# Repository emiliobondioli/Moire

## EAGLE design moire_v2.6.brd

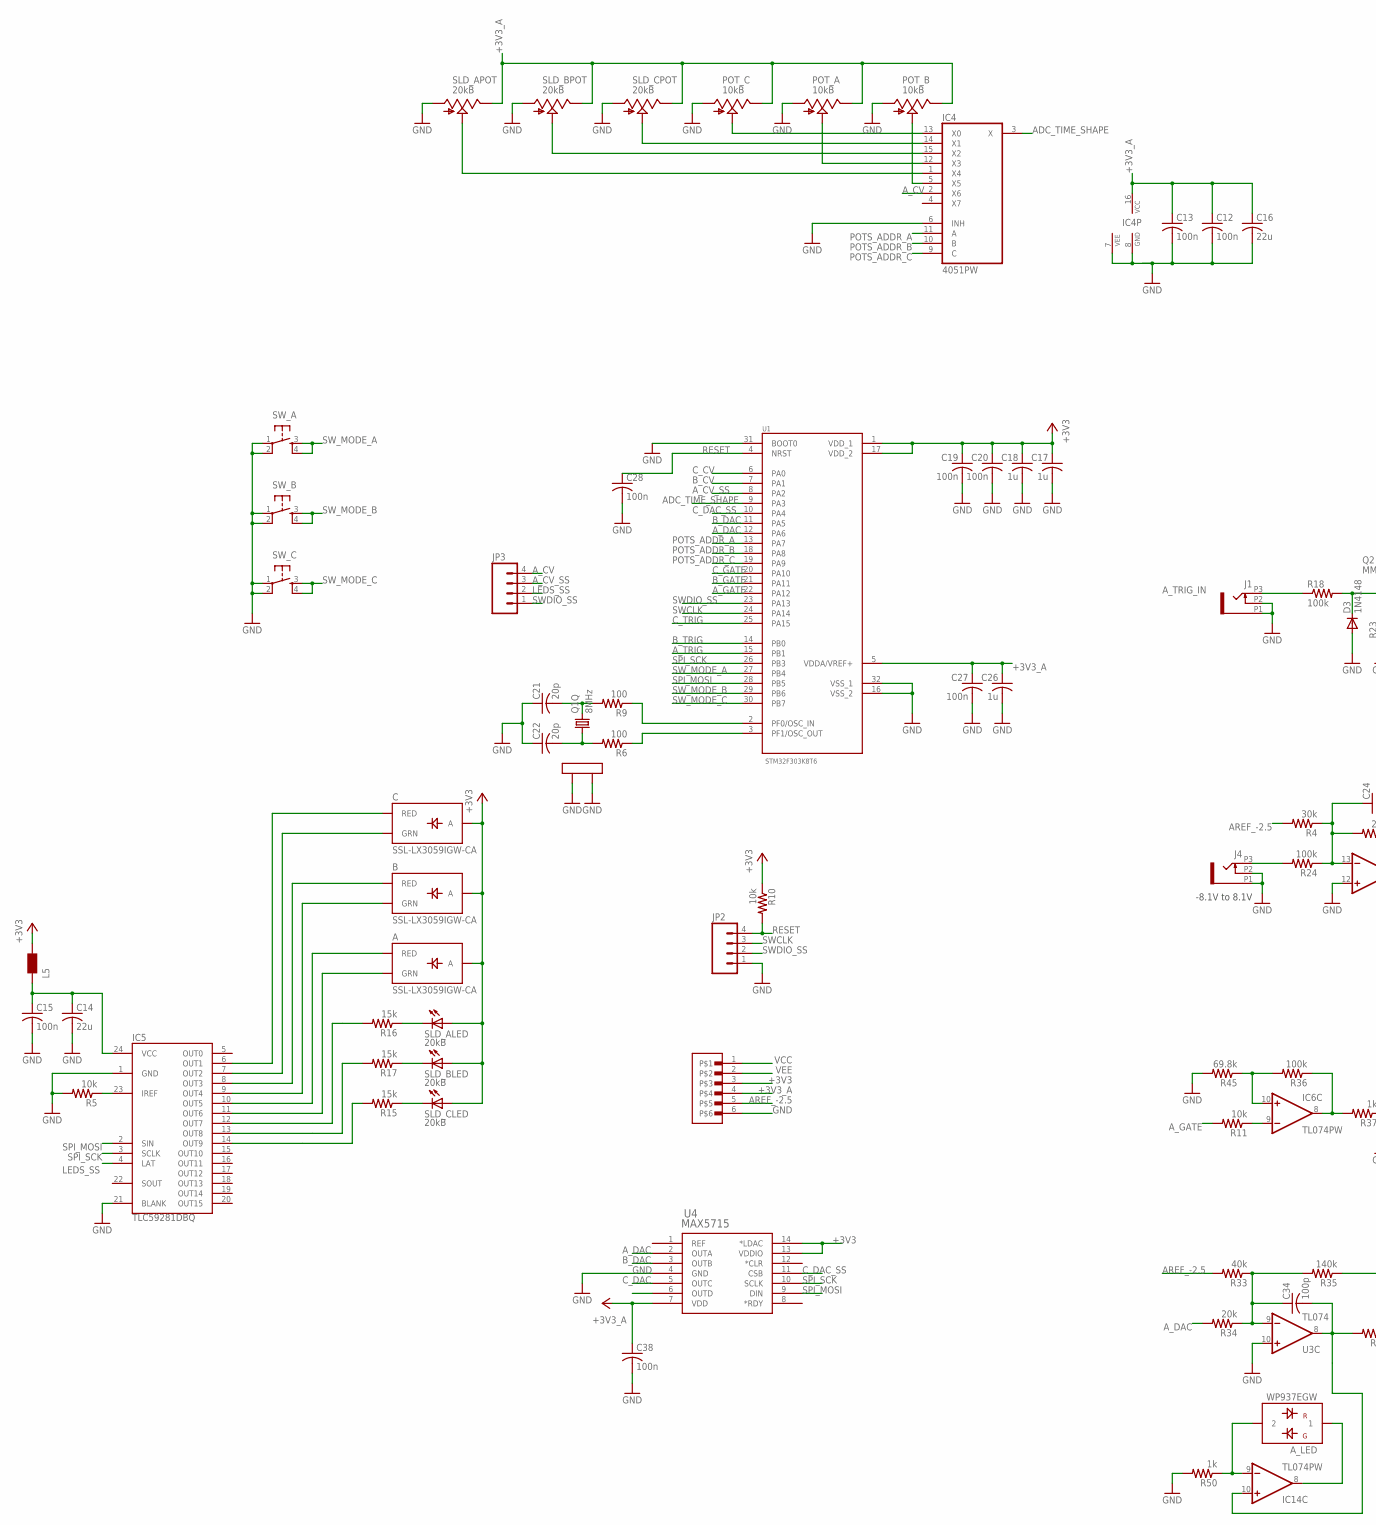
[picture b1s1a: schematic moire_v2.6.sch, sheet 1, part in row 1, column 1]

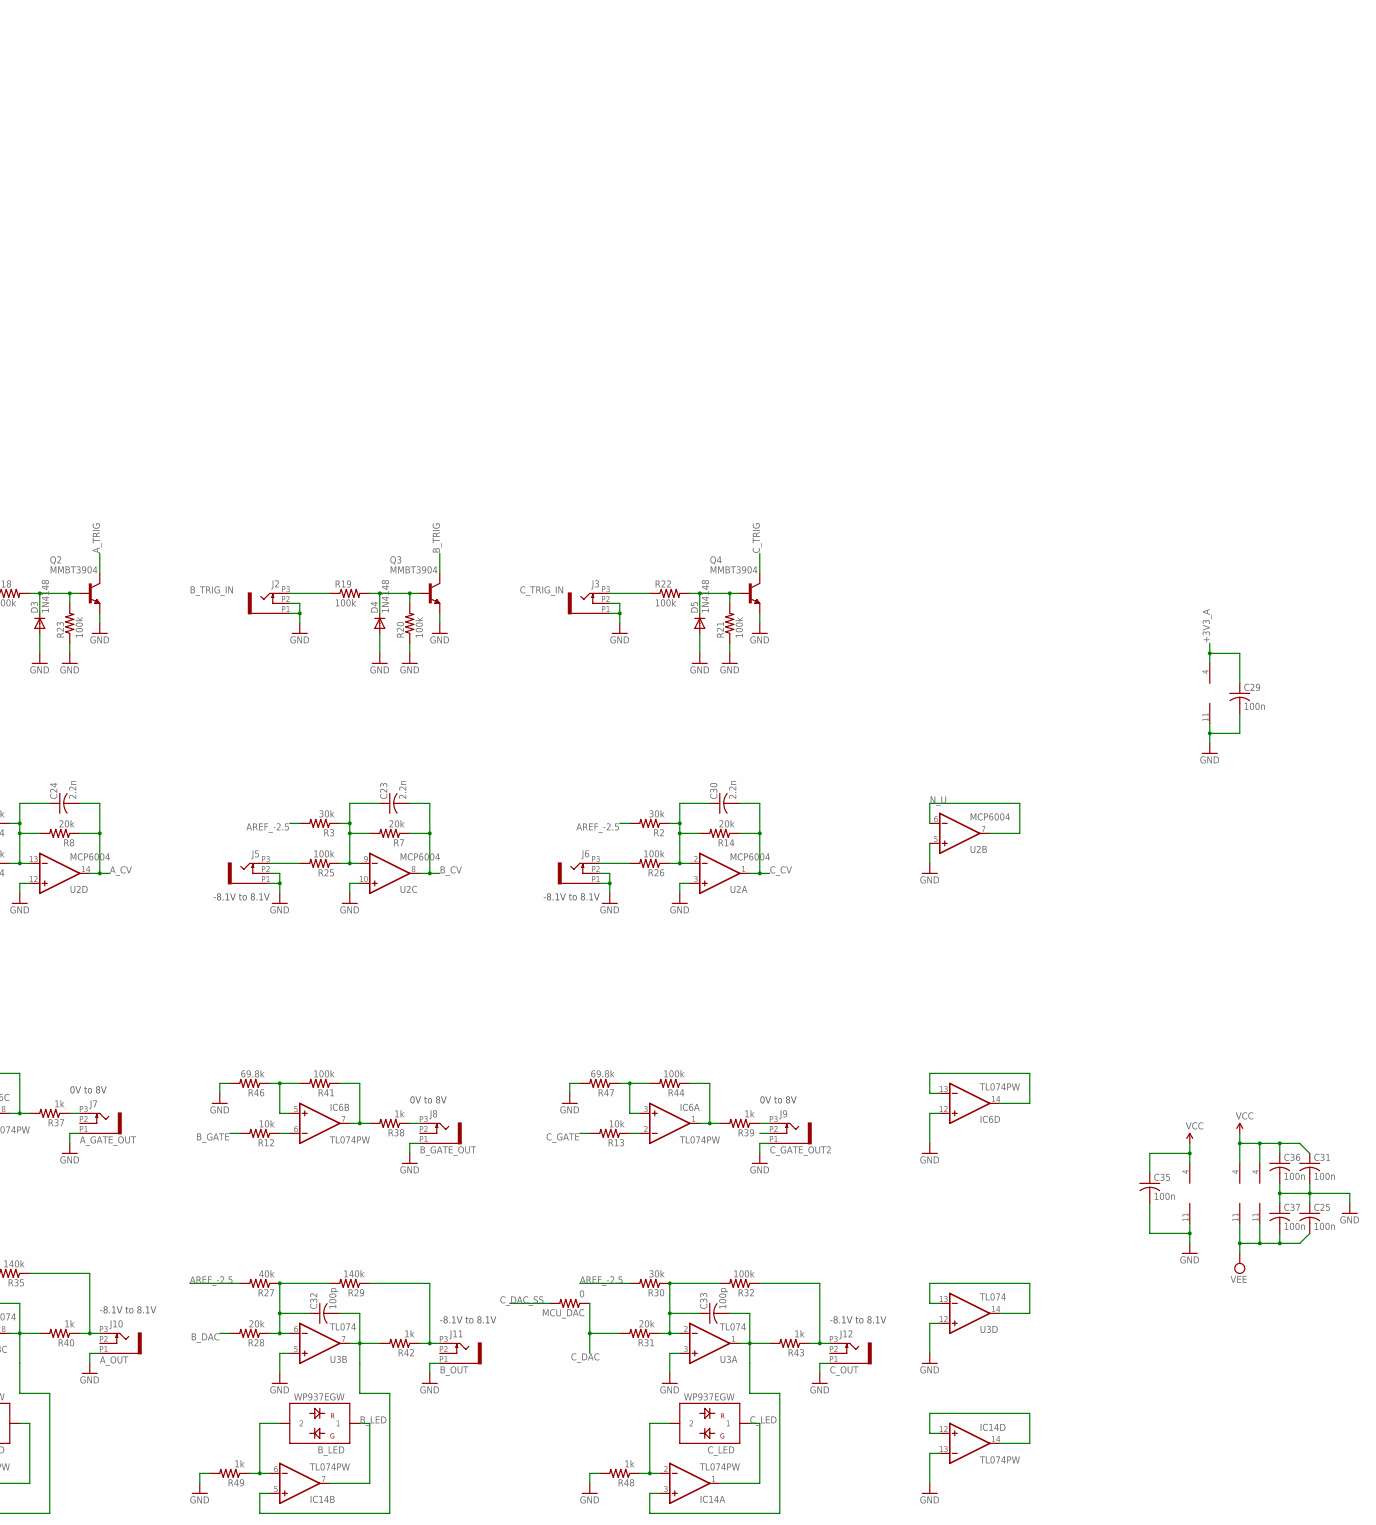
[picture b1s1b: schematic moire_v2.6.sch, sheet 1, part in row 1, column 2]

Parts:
A: SSL-LX3059IGW-CA; LED-BICOLOR-THROUGHHOLE-LUMEX
A_LED: WP937EGW; LED3MM
B: SSL-LX3059IGW-CA; LED-BICOLOR-THROUGHHOLE-LUMEX
B_LED: WP937EGW; LED3MM
C: SSL-LX3059IGW-CA; LED-BICOLOR-THROUGHHOLE-LUMEX
C12, C13, C15, C19, C20, C25, C27, C28, C29, C31, C35, C36, C37, C38: 100n; RCL_C0603
C14, C16: 22u; RCL_C1206
C17, C18, C26: 1u; RCL_C0603
C21, C22: 20p; RCL_C0603
C23, C24, C30: 2.2n; RCL_C0603
C32, C33, C34: 100p; RCL_C0603
C_LED: WP937EGW; LED3MM
D3, D4, D5: 1N4148; DIODE_SOD323-R
IC4: 4051PW; TSSOP16_065
IC5: TLC59281DBQ; TSSOP24_0635
IC6, IC14: TL074PW; TSSOP14_065
J1, J2, J3, J4, J5, J6, J7, J8, J9, J10, J11, J12: PJ301_THONKICONN6; WQP_PJ_301M6
JP2, JP3: M04PTH; 1X04
L5: WE-CBF_0603; 0603
MCU_DAC: 0; RCL_R0603
POT_A: 10kB; ALPS_POT_VERTICAL
POT_B: 10kB; ALPS_POT_VERTICAL
POT_C: 10kB; ALPS_POT_VERTICAL
Q1: 8MHz; CTS406
Q2, Q3, Q4: MMBT3904; SOT23-BEC
R2, R3, R4, R30: 30k; RCL_R0603
R5, R10, R11, R12, R13: 10k; RCL_R0603
R6, R9: 100; RCL_R0603
R7, R8, R14, R28, R31, R34: 20k; RCL_R0603
R15, R16, R17: 15k; RCL_R0603
R18, R19, R20, R21, R22, R23, R24, R25, R26, R32, R36, R41, R44: 100k; RCL_R0603
R27, R33: 40k; RCL_R0603
R29, R35: 140k; RCL_R0603
R37, R38, R39, R40, R42, R43, R48, R49, R50: 1k; RCL_R0603
R45, R46, R47: 69.8k; RCL_R0603
SLD_A: 20kB; BOURNS_SLIDER
SLD_B: 20kB; BOURNS_SLIDER
SLD_C: 20kB; BOURNS_SLIDER
SW_A: TAC_SWITCHPTH; TACTILE-PTH
SW_B: TAC_SWITCHPTH; TACTILE-PTH
SW_C: TAC_SWITCHPTH; TACTILE-PTH
U1: STM32F303K8T6; QFP80P900X900X160-32N
U2: MCP6004; SO14
U3: TL074; SO14
U4: MAX5715; 21-0066J_14
U$1: 1X6-SMD-TESTPAD; 6X1-SMD-TESTPAD

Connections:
+3V3_A: C12.1, C13.1, C16.1, C26.1, C27.1, C29.1, C38.1, IC4.16 (VCC), POT_A.P$1 (E), POT_B.P$1 (E), POT_C.P$1 (E), SLD_A.3 (E), SLD_B.3 (E), SLD_C.3 (E), U1.5 (VDDA/VREF+), U2.4 (V+), U4.7 (VDD), U$1.4; also elsewhere on the board
ADC_TIME_SHAPE: IC4.3 (X), U1.9 (PA3)
AREF_-2.5: R2.2, R3.2, R4.2, R27.2, R30.2, R33.2, U$1.5; also elsewhere on the board
A_CV: C24.2, IC4.2 (X6), JP3.4, R8.1, U2.14 (OUT)
A_CV_IN: J4.P3 (3), R24.2
A_CV_SS: JP3.3, U1.8 (PA2)
A_DAC: R34.2, U1.12 (PA6), U4.2 (OUTA)
A_GATE: R11.2, U1.22 (PA12)
A_GATE_OUT: J7.P3 (3), R37.1
A_LED: A_LED.1, IC14.8 (OUT)
A_OUT: J10.P3 (3), R35.1, R40.1
A_POT: IC4.12 (X3), POT_A.P$2 (S)
A_SLD: IC4.1 (X4), SLD_A.2 (S)
A_TRIG: Q2.C, U1.15 (PB1)
A_TRIG_IN: J1.P3 (3), R18.1
B_CV: C23.2, R7.1, U1.7 (PA1), U2.8 (OUT)
B_CV_IN: J5.P3 (3), R25.2
B_GATE: R12.2, U1.21 (PA11)
B_GATE_OUT: J8.P3 (3), R38.1
B_LED: B_LED.1, IC14.7 (OUT)
B_OUT: J11.P3 (3), R29.1, R42.1
B_POT: IC4.5 (X5), POT_B.P$2 (S)
B_SLD: IC4.15 (X2), SLD_B.2 (S)
B_TRIG: Q3.C, U1.14 (PB0)
B_TRIG_IN: J2.P3 (3), R19.1
C_CV: C30.2, R14.1, U1.6 (PA0), U2.1 (OUT)
C_CV_IN: J6.P3 (3), R26.2
C_DAC: MCU_DAC.1, R31.2, U4.5 (OUTC)
C_DAC_SS: MCU_DAC.2, U1.10 (PA4), U4.11 (CSB)
C_GATE: R13.2, U1.20 (PA10)
C_GATE_OUT2: J9.P3 (3), R39.1
C_LED: C_LED.1, IC14.1 (OUT)
C_OUT: J12.P3 (3), R32.1, R43.1
C_POT: IC4.13 (X0), POT_C.P$2 (S)
C_SLD: IC4.14 (X1), SLD_C.2 (S)
C_TRIG: Q4.C, U1.25 (PA15)
C_TRIG_IN: J3.P3 (3), R22.1
GND: C12.2, C13.2, C14.2, C15.2, C16.2, C17.2, C18.2, C19.2, C20.2, C21.1, C22.1, C25.1, C26.2, C27.2, C28.2, C29.2, C31.2, C35.2, C36.2, C37.1, C38.2, D3.A, D4.A, D5.A, IC4.6 (INH), IC4.7 (VEE), IC4.8 (GND), IC5.1 (GND), IC5.21 (BLANK), IC6.11 (V-), IC6.12 (+IN), IC14.13 (-IN), J1.P1 (1), J1.P2 (2), J2.P1 (1), J2.P2 (2), J3.P1 (1), J3.P2 (2), J4.P1 (1), J4.P2 (2), J5.P1 (1), J5.P2 (2), J6.P1 (1), J6.P2 (2), J7.P1 (1), J8.P1 (1), J9.P1 (1), J10.P1 (1), J11.P1 (1), J12.P1 (1), JP2.1, POT_A.P$3 (A), POT_B.P$3 (A), POT_C.P$3 (A), Q1.2 (LID1), Q1.4 (LID2), Q2.E, Q3.E, Q4.E, R5.2, R20.1, R21.1, R23.1, R45.2, R46.2, R47.2, R48.2, R49.2, R50.2, SLD_A.1 (A), SLD_B.1 (A), SLD_C.1 (A), SW_A.1, SW_A.2, SW_B.1, SW_B.2, SW_C.1, SW_C.2, U1.16 (VSS_2), U1.31 (BOOT0), U1.32 (VSS_1), U2.3 (+IN), U2.5 (+IN), U2.10 (+IN), U2.11 (V-), U2.12 (+IN), U3.3 (+IN), U3.5 (+IN), U3.10 (+IN), U3.12 (+IN), U4.4 (GND), U$1.6; also elsewhere on the board
LEDS_SS: IC5.4 (LAT), JP3.2
unnamed: IC5.12 (OUT7), R16.2
unnamed: IC6.13 (-IN), IC6.14 (OUT)
unnamed: C32.1, R27.1, R28.1, R29.2, U3.6 (-IN)
unnamed: R9.1, U1.2 (PF0/OSC_IN)
unnamed: R6.1, U1.3 (PF1/OSC_OUT)
unnamed: C21.2, Q1.3 (2), R9.2
unnamed: C22.2, Q1.1, R6.2
unnamed: U3.13 (-IN), U3.14 (OUT)
unnamed: C32.2, IC14.5 (+IN), R42.2, U3.7 (OUT)
unnamed: IC6.1 (OUT), R39.2, R44.1
unnamed: C34.1, R33.1, R34.1, R35.2, U3.9 (-IN)
unnamed: C34.2, IC14.10 (+IN), R40.2, U3.8 (OUT)
unnamed: IC6.3 (+IN), R44.2, R47.1
unnamed: IC6.2 (-IN), R13.1
unnamed: IC6.7 (OUT), R38.2, R41.1
unnamed: R16.1, SLD_A.E (C)
unnamed: IC6.5 (+IN), R41.2, R46.1
unnamed: IC6.6 (-IN), R12.1
unnamed: IC6.8 (OUT), R36.1, R37.2
unnamed: IC14.12 (+IN), IC14.14 (OUT)
unnamed: C.RED_C (RED), IC5.6 (OUT1)
unnamed: C.GREEN_C (GRN), IC5.7 (OUT2)
unnamed: B.RED_C (RED), IC5.8 (OUT3)
unnamed: B.GREEN_C (GRN), IC5.9 (OUT4)
unnamed: A.RED_C (RED), IC5.10 (OUT5)
unnamed: A.GREEN_C (GRN), IC5.11 (OUT6)
unnamed: IC5.13 (OUT8), R17.2
unnamed: IC5.14 (OUT9), R15.2
unnamed: B_LED.2, IC14.6 (-IN), R49.1
unnamed: D3.C, Q2.B, R18.2, R23.2
unnamed: R17.1, SLD_B.E (C)
unnamed: C14.1, C15.1, IC5.24 (VCC), L5.1
unnamed: R15.1, SLD_C.E (C)
unnamed: A_LED.2, IC14.9 (-IN), R50.1
unnamed: C30.1, R2.1, R14.2, R26.1, U2.2 (-IN)
unnamed: C23.1, R3.1, R7.2, R25.1, U2.9 (-IN)
unnamed: C24.1, R4.1, R8.2, R24.1, U2.13 (-IN)
unnamed: IC6.10 (+IN), R36.2, R45.1
unnamed: D4.C, Q3.B, R19.2, R20.2
unnamed: IC6.9 (-IN), R11.1
unnamed: D5.C, Q4.B, R21.2, R22.2
unnamed: IC5.23 (IREF), R5.1
unnamed: C_LED.2, IC14.2 (-IN), R48.1
unnamed: C33.1, R30.1, R31.1, R32.2, U3.2 (-IN)
unnamed: C33.2, IC14.3 (+IN), R43.2, U3.1 (OUT)
N_U: U2.6 (-IN), U2.7 (OUT)
POTS_ADDR_A: IC4.11 (A), U1.13 (PA7)
POTS_ADDR_B: IC4.10 (B), U1.18 (PA8)
POTS_ADDR_C: IC4.9 (C), U1.19 (PA9)
RESET: C28.1, JP2.4, R10.2, U1.4 (NRST)
SPI_MOSI: IC5.2 (SIN), U1.28 (PB5), U4.9 (DIN)
SPI_SCK: IC5.3 (SCLK), U1.26 (PB3), U4.10 (SCLK)
SWCLK: JP2.3, U1.24 (PA14)
SWDIO_SS: JP2.2, JP3.1, U1.23 (PA13)
SW_MODE_A: SW_A.3, SW_A.4, U1.27 (PB4)
SW_MODE_B: SW_B.3, SW_B.4, U1.29 (PB6)
SW_MODE_C: SW_C.3, SW_C.4, U1.30 (PB7)
VCC: C31.1, C35.1, C36.1, IC6.4 (V+), IC14.4 (V+), U3.4 (V+), U$1.1; also elsewhere on the board
VEE: C25.2, C37.2, IC14.11 (V-), U3.11 (V-), U$1.2; also elsewhere on the board

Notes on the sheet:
-8.1V to 8.1V
0V to 8V

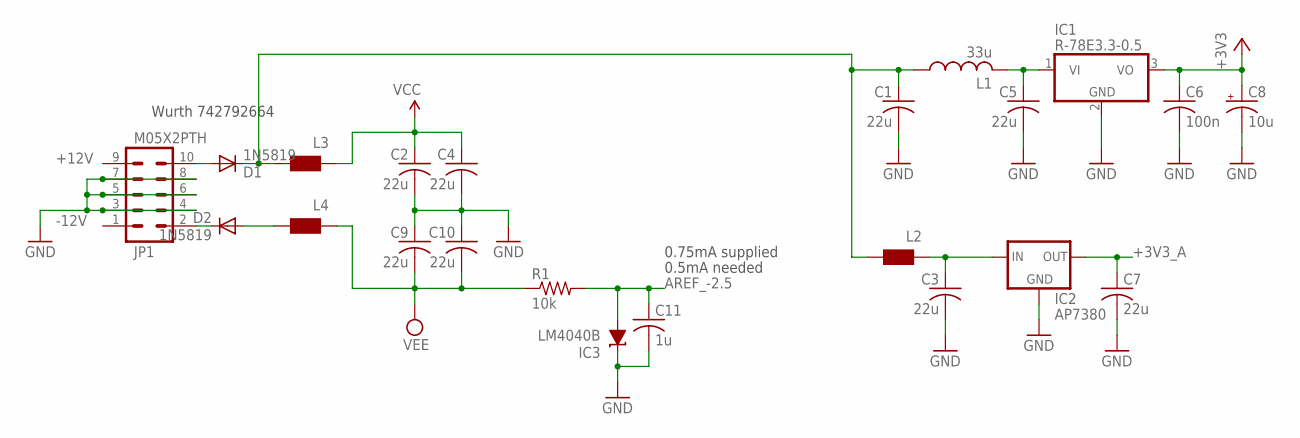
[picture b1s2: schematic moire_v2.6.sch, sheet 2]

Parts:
C1, C2, C3, C4, C5, C7, C9, C10: 22u; RCL_C1206
C6: 100n; RCL_C0603
C8: 10u; RCL_PANASONIC_A
C11: 1u; RCL_C0603
D1, D2: 1N5819; DIODE_SOD123
IC1: R-78E3.3-0.5; WE78
IC2: AP7380; SOT89
IC3: LM4040B; DBZ_R-PDSO-G3
JP1: M05X2PTH; 2X5-PTH
L1: 33u; L2012C
L2, L3, L4: WE-CBF_0603; 0603
R1: 10k; RCL_R0603

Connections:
+3V3_A: C7.1, IC2.3 (OUT); also elsewhere on the board
+12V: D1.A, JP1.9, JP1.10
-12V: D2.C, JP1.1, JP1.2
AREF_-2.5: C11.1, IC3.2 (A), R1.2; also elsewhere on the board
GND: C1.2, C2.2, C3.2, C4.2, C5.2, C6.2, C7.2, C8.-, C9.1, C10.1, C11.2, IC1.2 (GND), IC2.1 (GND), IC3.1 (C), JP1.3, JP1.4, JP1.5, JP1.6, JP1.7, JP1.8; also elsewhere on the board
unnamed: D2.A, L4.2
unnamed: C1.1, D1.C, L1.1, L2.2, L3.2
unnamed: C3.1, IC2.2 (IN), IC2.4 (IN), L2.1
unnamed: C5.1, IC1.1 (VI), L1.2
VCC: C2.1, C4.1, L3.1; also elsewhere on the board
VEE: C9.2, C10.2, L4.1, R1.1; also elsewhere on the board

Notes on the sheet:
0.5mA needed
Wurth 742792664
0.75mA supplied

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
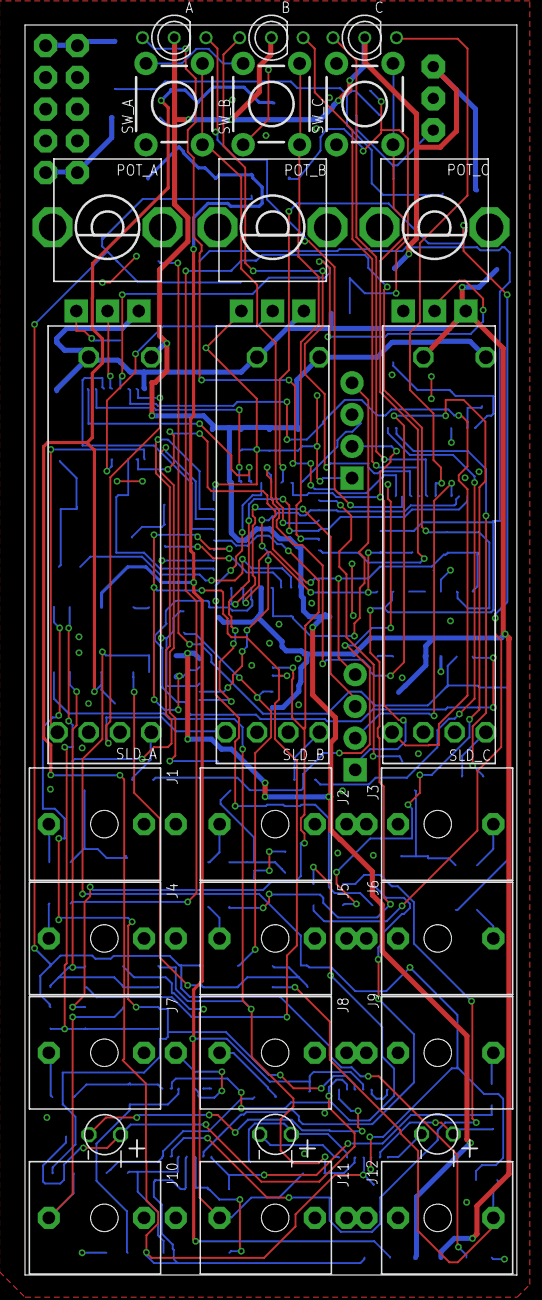
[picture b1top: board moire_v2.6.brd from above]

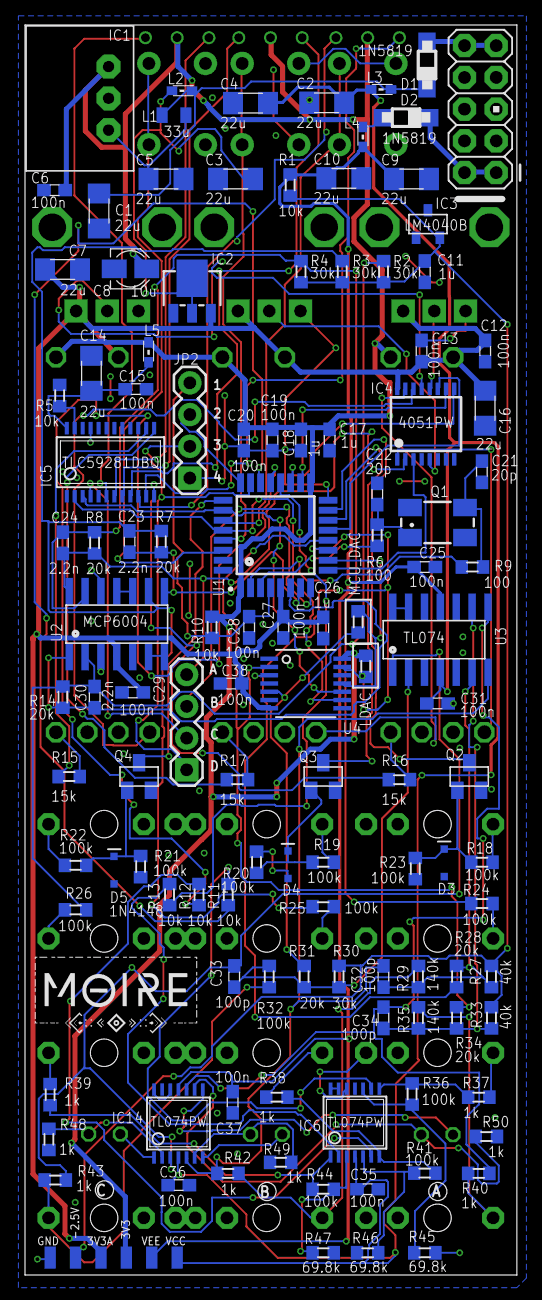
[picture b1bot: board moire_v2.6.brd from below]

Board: 2 copper layers, 39.4 x 100.0 mm, 146 parts (119 on the bottom side), 106 nets.

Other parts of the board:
LDAC: 0; RCL_R0603

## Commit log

2018-10-21 update sch
2018-10-22 update brd
2018-10-22 update board
2018-10-23 finish placement and begin routing
2018-10-23 finish routing
2018-10-23 resolve drc errors
2018-10-24 finishing touches
2018-10-25 create 1.9 prototype with 100mm board
2018-11-18 apply fixes from prototype
2018-11-19 align C slider
2018-12-02 add optional dac and fix names on schematic
